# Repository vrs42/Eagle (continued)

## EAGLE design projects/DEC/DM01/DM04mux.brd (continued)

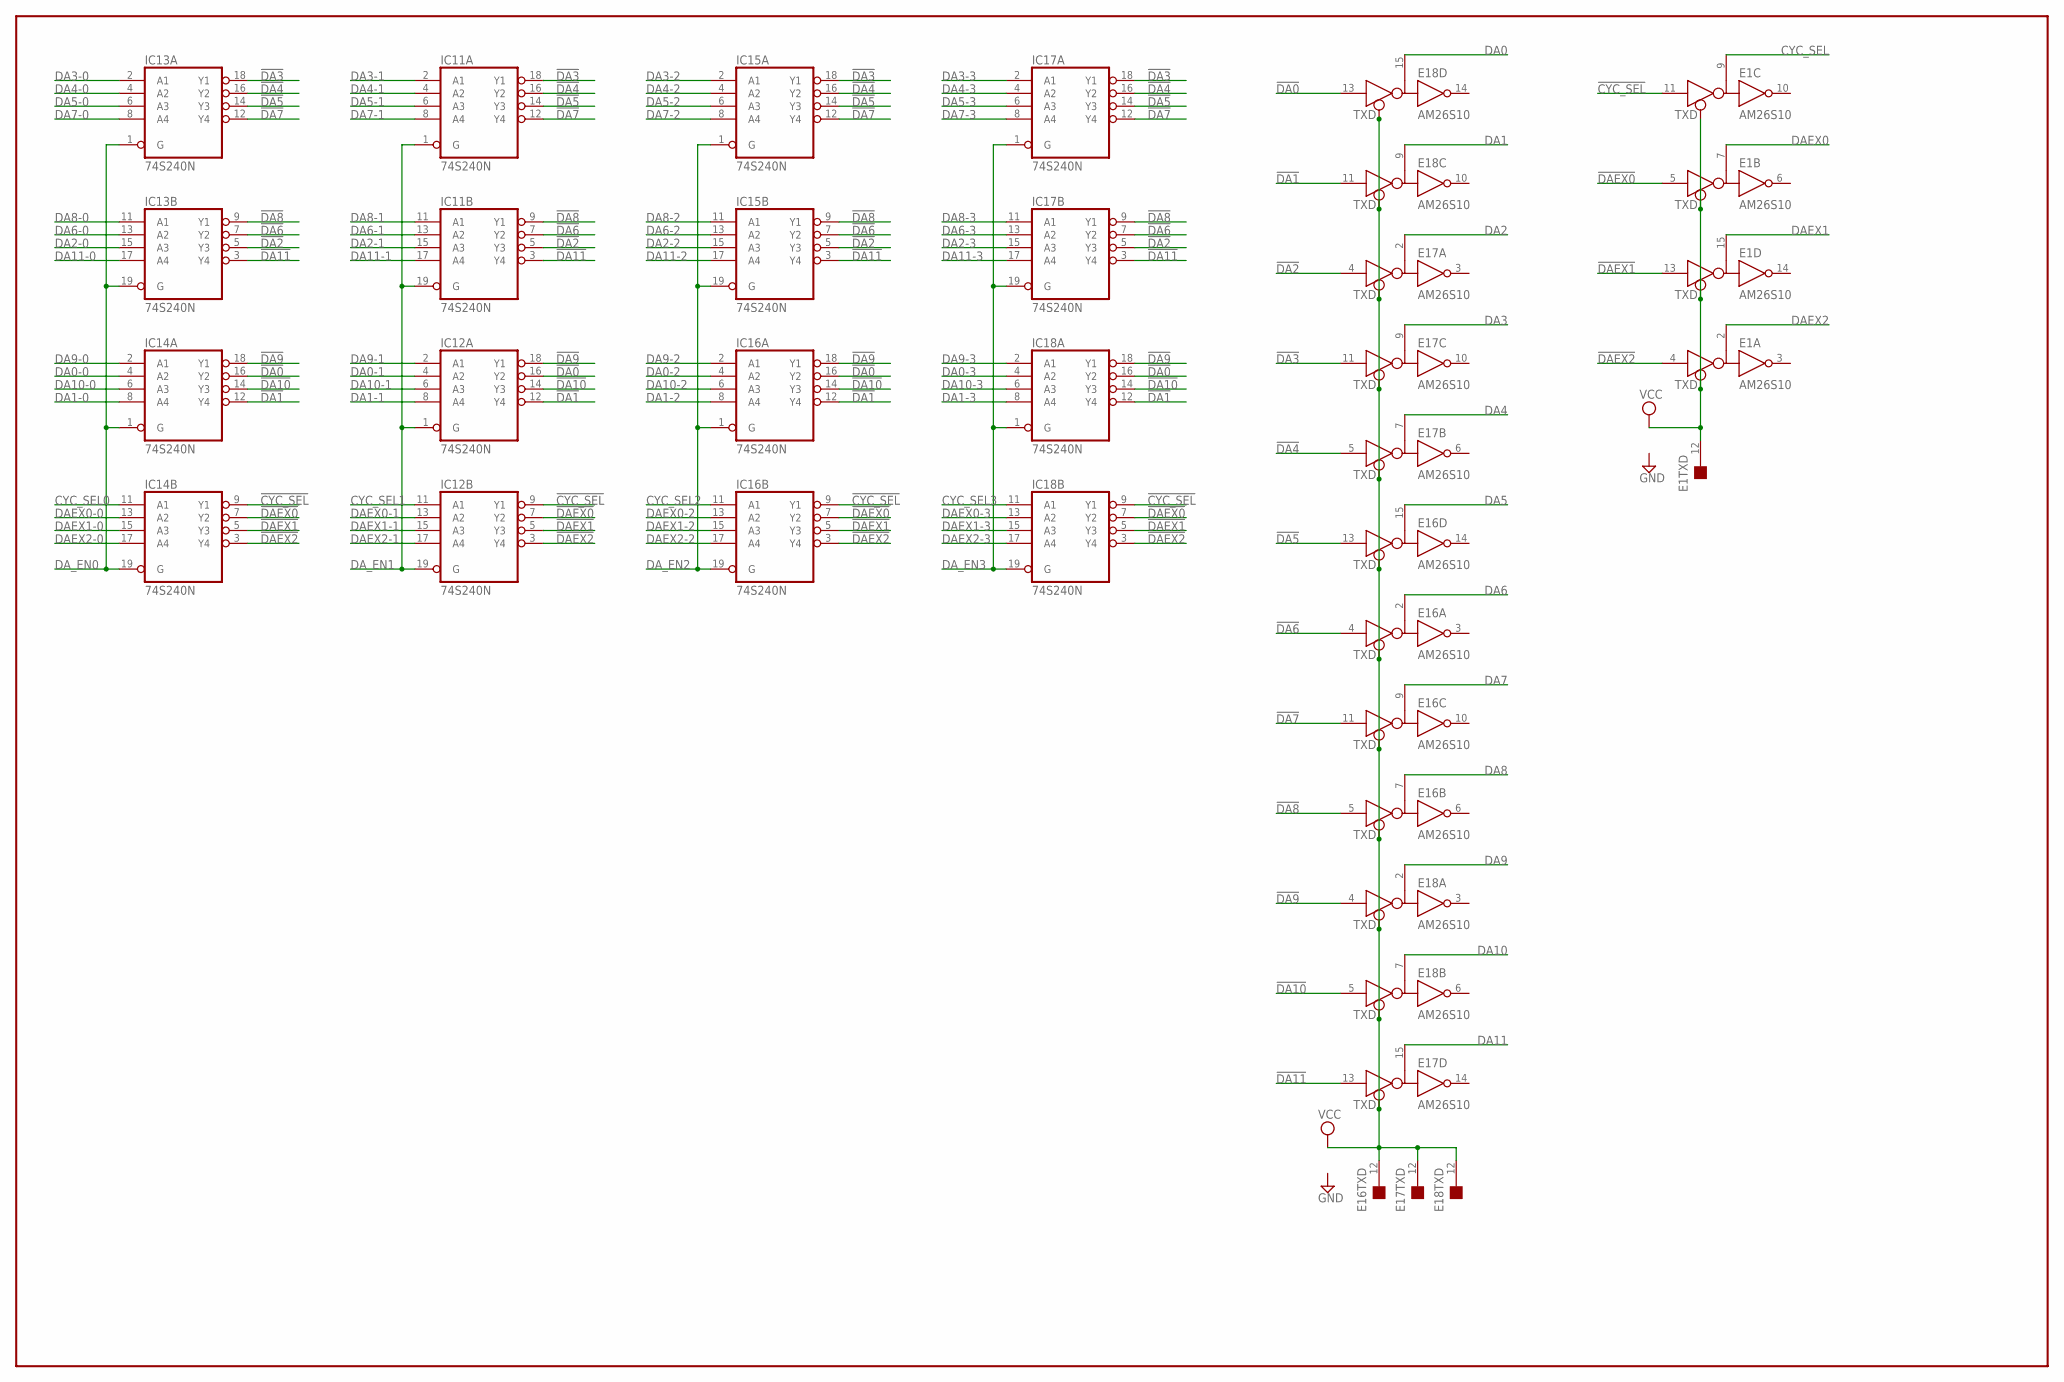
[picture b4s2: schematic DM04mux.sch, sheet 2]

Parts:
E1, E16, E17, E18: AM26S10; DIL16
IC11, IC12, IC13, IC14, IC15, IC16, IC17, IC18: 74S240N; DIL20

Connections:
!CYC_SEL: E1.11 (D), IC12.9 (Y1), IC14.9 (Y1), IC16.9 (Y1), IC18.9 (Y1)
!DA0: E18.13 (D), IC12.16 (Y2), IC14.16 (Y2), IC16.16 (Y2), IC18.16 (Y2)
!DA1: E18.11 (D), IC12.12 (Y4), IC14.12 (Y4), IC16.12 (Y4), IC18.12 (Y4)
!DA2: E17.4 (D), IC11.5 (Y3), IC13.5 (Y3), IC15.5 (Y3), IC17.5 (Y3)
!DA3: E17.11 (D), IC11.18 (Y1), IC13.18 (Y1), IC15.18 (Y1), IC17.18 (Y1)
!DA4: E17.5 (D), IC11.16 (Y2), IC13.16 (Y2), IC15.16 (Y2), IC17.16 (Y2)
!DA5: E16.13 (D), IC11.14 (Y3), IC13.14 (Y3), IC15.14 (Y3), IC17.14 (Y3)
!DA6: E16.4 (D), IC11.7 (Y2), IC13.7 (Y2), IC15.7 (Y2), IC17.7 (Y2)
!DA7: E16.11 (D), IC11.12 (Y4), IC13.12 (Y4), IC15.12 (Y4), IC17.12 (Y4)
!DA8: E16.5 (D), IC11.9 (Y1), IC13.9 (Y1), IC15.9 (Y1), IC17.9 (Y1)
!DA9: E18.4 (D), IC12.18 (Y1), IC14.18 (Y1), IC16.18 (Y1), IC18.18 (Y1)
!DA10: E18.5 (D), IC12.14 (Y3), IC14.14 (Y3), IC16.14 (Y3), IC18.14 (Y3)
!DA11: E17.13 (D), IC11.3 (Y4), IC13.3 (Y4), IC15.3 (Y4), IC17.3 (Y4)
!DAEX0: E1.5 (D), IC12.7 (Y2), IC14.7 (Y2), IC16.7 (Y2), IC18.7 (Y2)
!DAEX1: E1.13 (D), IC12.5 (Y3), IC14.5 (Y3), IC16.5 (Y3), IC18.5 (Y3)
!DAEX2: E1.4 (D), IC12.3 (Y4), IC14.3 (Y4), IC16.3 (Y4), IC18.3 (Y4)
CYC_SEL: E1.9 (B); also elsewhere on the board
CYC_SEL0: IC14.11 (A1); also elsewhere on the board
CYC_SEL1: IC12.11 (A1); also elsewhere on the board
CYC_SEL2: IC16.11 (A1); also elsewhere on the board
CYC_SEL3: IC18.11 (A1); also elsewhere on the board
DA0: E18.15 (B); also elsewhere on the board
DA0-0: IC14.4 (A2); also elsewhere on the board
DA0-1: IC12.4 (A2); also elsewhere on the board
DA0-2: IC16.4 (A2); also elsewhere on the board
DA0-3: IC18.4 (A2); also elsewhere on the board
DA1: E18.9 (B); also elsewhere on the board
DA1-0: IC14.8 (A4); also elsewhere on the board
DA1-1: IC12.8 (A4); also elsewhere on the board
DA1-2: IC16.8 (A4); also elsewhere on the board
DA1-3: IC18.8 (A4); also elsewhere on the board
DA2: E17.2 (B); also elsewhere on the board
DA2-0: IC13.15 (A3); also elsewhere on the board
DA2-1: IC11.15 (A3); also elsewhere on the board
DA2-2: IC15.15 (A3); also elsewhere on the board
DA2-3: IC17.15 (A3); also elsewhere on the board
DA3: E17.9 (B); also elsewhere on the board
DA3-0: IC13.2 (A1); also elsewhere on the board
DA3-1: IC11.2 (A1); also elsewhere on the board
DA3-2: IC15.2 (A1); also elsewhere on the board
DA3-3: IC17.2 (A1); also elsewhere on the board
DA4: E17.7 (B); also elsewhere on the board
DA4-0: IC13.4 (A2); also elsewhere on the board
DA4-1: IC11.4 (A2); also elsewhere on the board
DA4-2: IC15.4 (A2); also elsewhere on the board
DA4-3: IC17.4 (A2); also elsewhere on the board
DA5: E16.15 (B); also elsewhere on the board
DA5-0: IC13.6 (A3); also elsewhere on the board
DA5-1: IC11.6 (A3); also elsewhere on the board
DA5-2: IC15.6 (A3); also elsewhere on the board
DA5-3: IC17.6 (A3); also elsewhere on the board
DA6: E16.2 (B); also elsewhere on the board
DA6-0: IC13.13 (A2); also elsewhere on the board
DA6-1: IC11.13 (A2); also elsewhere on the board
DA6-2: IC15.13 (A2); also elsewhere on the board
DA6-3: IC17.13 (A2); also elsewhere on the board
DA7: E16.9 (B); also elsewhere on the board
DA7-0: IC13.8 (A4); also elsewhere on the board
DA7-1: IC11.8 (A4); also elsewhere on the board
DA7-2: IC15.8 (A4); also elsewhere on the board
DA7-3: IC17.8 (A4); also elsewhere on the board
DA8: E16.7 (B); also elsewhere on the board
DA8-0: IC13.11 (A1); also elsewhere on the board
DA8-1: IC11.11 (A1); also elsewhere on the board
DA8-2: IC15.11 (A1); also elsewhere on the board
DA8-3: IC17.11 (A1); also elsewhere on the board
DA9: E18.2 (B); also elsewhere on the board
DA9-0: IC14.2 (A1); also elsewhere on the board
DA9-1: IC12.2 (A1); also elsewhere on the board
DA9-2: IC16.2 (A1); also elsewhere on the board
DA9-3: IC18.2 (A1); also elsewhere on the board
DA10: E18.7 (B); also elsewhere on the board
DA10-0: IC14.6 (A3); also elsewhere on the board
DA10-1: IC12.6 (A3); also elsewhere on the board
DA10-2: IC16.6 (A3); also elsewhere on the board
DA10-3: IC18.6 (A3); also elsewhere on the board
DA11: E17.15 (B); also elsewhere on the board
DA11-0: IC13.17 (A4); also elsewhere on the board
DA11-1: IC11.17 (A4); also elsewhere on the board
DA11-2: IC15.17 (A4); also elsewhere on the board
DA11-3: IC17.17 (A4); also elsewhere on the board
DAEX0: E1.7 (B); also elsewhere on the board
DAEX0-0: IC14.13 (A2); also elsewhere on the board
DAEX0-1: IC12.13 (A2); also elsewhere on the board
DAEX0-2: IC16.13 (A2); also elsewhere on the board
DAEX0-3: IC18.13 (A2); also elsewhere on the board
DAEX1: E1.15 (B); also elsewhere on the board
DAEX1-0: IC14.15 (A3); also elsewhere on the board
DAEX1-1: IC12.15 (A3); also elsewhere on the board
DAEX1-2: IC16.15 (A3); also elsewhere on the board
DAEX1-3: IC18.15 (A3); also elsewhere on the board
DAEX2: E1.2 (B); also elsewhere on the board
DAEX2-0: IC14.17 (A4); also elsewhere on the board
DAEX2-1: IC12.17 (A4); also elsewhere on the board
DAEX2-2: IC16.17 (A4); also elsewhere on the board
DAEX2-3: IC18.17 (A4); also elsewhere on the board
DA_EN0: IC13.1 (G), IC13.19 (G), IC14.1 (G), IC14.19 (G); also elsewhere on the board
DA_EN1: IC11.1 (G), IC11.19 (G), IC12.1 (G), IC12.19 (G); also elsewhere on the board
DA_EN2: IC15.1 (G), IC15.19 (G), IC16.1 (G), IC16.19 (G); also elsewhere on the board
DA_EN3: IC17.1 (G), IC17.19 (G), IC18.1 (G), IC18.19 (G); also elsewhere on the board
GND: E1.1 (GND), E1.8 (GND), E16.1 (GND), E16.8 (GND), E17.1 (GND), E17.8 (GND), E18.1 (GND), E18.8 (GND), IC11.10 (GND), IC12.10 (GND), IC13.10 (GND), IC14.10 (GND), IC15.10 (GND), IC16.10 (GND), IC17.10 (GND), IC18.10 (GND); also elsewhere on the board
VCC: E1.12 (TXD), E1.16 (VCC), E16.12 (TXD), E16.16 (VCC), E17.12 (TXD), E17.16 (VCC), E18.12 (TXD), E18.16 (VCC), IC11.20 (VCC), IC12.20 (VCC), IC13.20 (VCC), IC14.20 (VCC), IC15.20 (VCC), IC16.20 (VCC), IC17.20 (VCC), IC18.20 (VCC); also elsewhere on the board

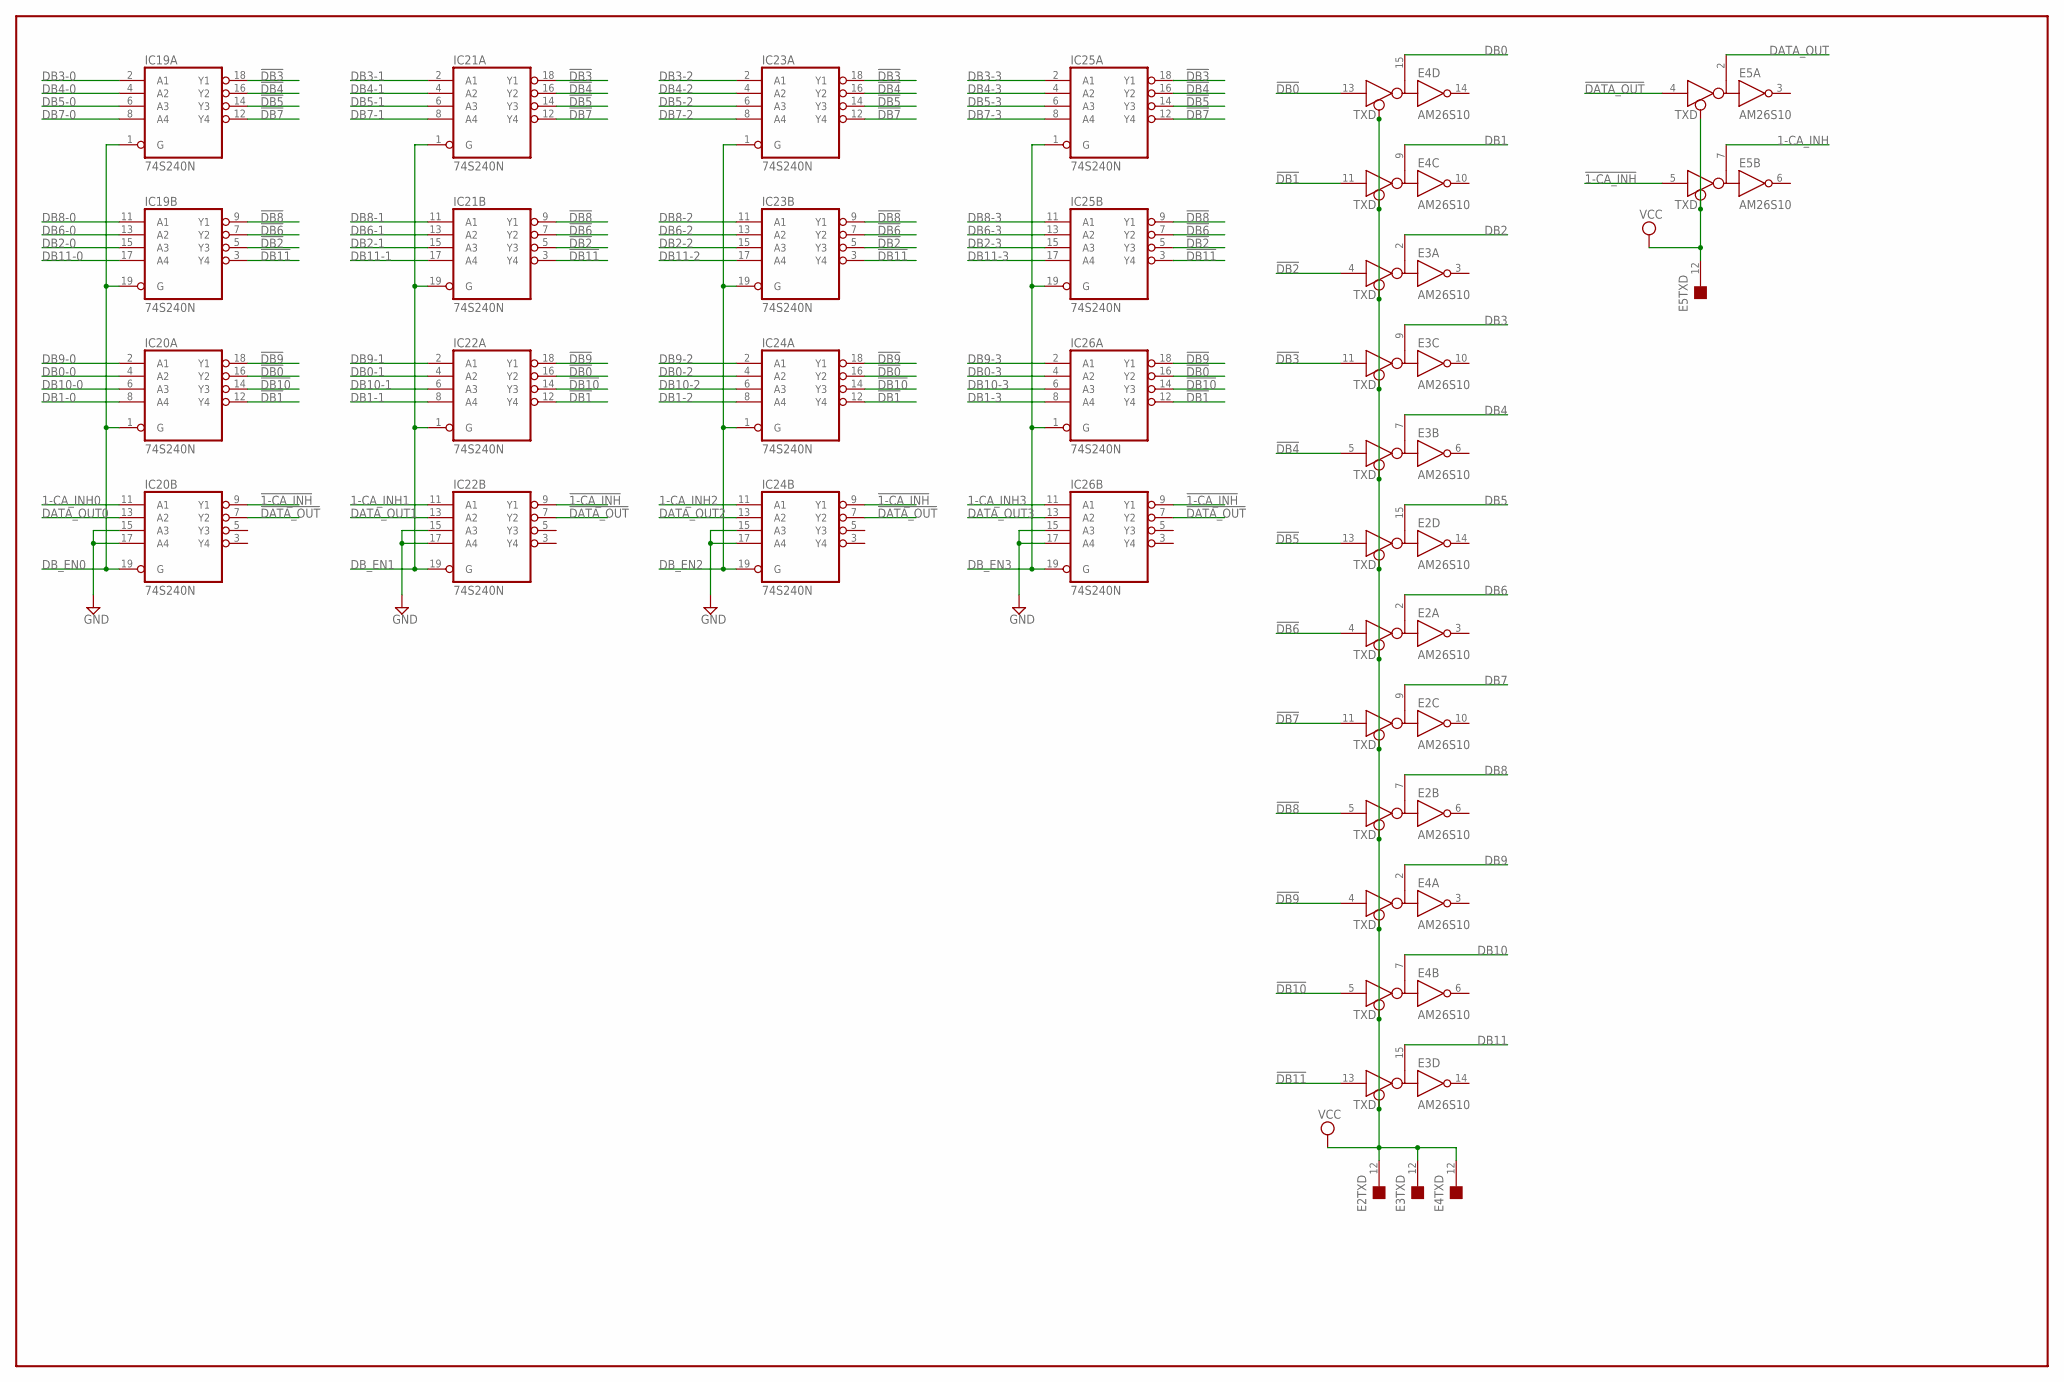
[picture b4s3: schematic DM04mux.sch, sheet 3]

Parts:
E2, E3, E4, E5: AM26S10; DIL16
IC19, IC20, IC21, IC22, IC23, IC24, IC25, IC26: 74S240N; DIL20

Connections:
1-CA_INH: E5.7 (B); also elsewhere on the board
1-CA_INH0: IC20.11 (A1); also elsewhere on the board
1-CA_INH1: IC22.11 (A1); also elsewhere on the board
1-CA_INH2: IC24.11 (A1); also elsewhere on the board
1-CA_INH3: IC26.11 (A1); also elsewhere on the board
!1-CA_INH: E5.5 (D), IC20.9 (Y1), IC22.9 (Y1), IC24.9 (Y1), IC26.9 (Y1)
!DATA_OUT: E5.4 (D), IC20.7 (Y2), IC22.7 (Y2), IC24.7 (Y2), IC26.7 (Y2)
!DB0: E4.13 (D), IC20.16 (Y2), IC22.16 (Y2), IC24.16 (Y2), IC26.16 (Y2)
!DB1: E4.11 (D), IC20.12 (Y4), IC22.12 (Y4), IC24.12 (Y4), IC26.12 (Y4)
!DB2: E3.4 (D), IC19.5 (Y3), IC21.5 (Y3), IC23.5 (Y3), IC25.5 (Y3)
!DB3: E3.11 (D), IC19.18 (Y1), IC21.18 (Y1), IC23.18 (Y1), IC25.18 (Y1)
!DB4: E3.5 (D), IC19.16 (Y2), IC21.16 (Y2), IC23.16 (Y2), IC25.16 (Y2)
!DB5: E2.13 (D), IC19.14 (Y3), IC21.14 (Y3), IC23.14 (Y3), IC25.14 (Y3)
!DB6: E2.4 (D), IC19.7 (Y2), IC21.7 (Y2), IC23.7 (Y2), IC25.7 (Y2)
!DB7: E2.11 (D), IC19.12 (Y4), IC21.12 (Y4), IC23.12 (Y4), IC25.12 (Y4)
!DB8: E2.5 (D), IC19.9 (Y1), IC21.9 (Y1), IC23.9 (Y1), IC25.9 (Y1)
!DB9: E4.4 (D), IC20.18 (Y1), IC22.18 (Y1), IC24.18 (Y1), IC26.18 (Y1)
!DB10: E4.5 (D), IC20.14 (Y3), IC22.14 (Y3), IC24.14 (Y3), IC26.14 (Y3)
!DB11: E3.13 (D), IC19.3 (Y4), IC21.3 (Y4), IC23.3 (Y4), IC25.3 (Y4)
DATA_OUT: E5.2 (B); also elsewhere on the board
DATA_OUT0: IC20.13 (A2); also elsewhere on the board
DATA_OUT1: IC22.13 (A2); also elsewhere on the board
DATA_OUT2: IC24.13 (A2); also elsewhere on the board
DATA_OUT3: IC26.13 (A2); also elsewhere on the board
DB0: E4.15 (B); also elsewhere on the board
DB0-0: IC20.4 (A2); also elsewhere on the board
DB0-1: IC22.4 (A2); also elsewhere on the board
DB0-2: IC24.4 (A2); also elsewhere on the board
DB0-3: IC26.4 (A2); also elsewhere on the board
DB1: E4.9 (B); also elsewhere on the board
DB1-0: IC20.8 (A4); also elsewhere on the board
DB1-1: IC22.8 (A4); also elsewhere on the board
DB1-2: IC24.8 (A4); also elsewhere on the board
DB1-3: IC26.8 (A4); also elsewhere on the board
DB2: E3.2 (B); also elsewhere on the board
DB2-0: IC19.15 (A3); also elsewhere on the board
DB2-1: IC21.15 (A3); also elsewhere on the board
DB2-2: IC23.15 (A3); also elsewhere on the board
DB2-3: IC25.15 (A3); also elsewhere on the board
DB3: E3.9 (B); also elsewhere on the board
DB3-0: IC19.2 (A1); also elsewhere on the board
DB3-1: IC21.2 (A1); also elsewhere on the board
DB3-2: IC23.2 (A1); also elsewhere on the board
DB3-3: IC25.2 (A1); also elsewhere on the board
DB4: E3.7 (B); also elsewhere on the board
DB4-0: IC19.4 (A2); also elsewhere on the board
DB4-1: IC21.4 (A2); also elsewhere on the board
DB4-2: IC23.4 (A2); also elsewhere on the board
DB4-3: IC25.4 (A2); also elsewhere on the board
DB5: E2.15 (B); also elsewhere on the board
DB5-0: IC19.6 (A3); also elsewhere on the board
DB5-1: IC21.6 (A3); also elsewhere on the board
DB5-2: IC23.6 (A3); also elsewhere on the board
DB5-3: IC25.6 (A3); also elsewhere on the board
DB6: E2.2 (B); also elsewhere on the board
DB6-0: IC19.13 (A2); also elsewhere on the board
DB6-1: IC21.13 (A2); also elsewhere on the board
DB6-2: IC23.13 (A2); also elsewhere on the board
DB6-3: IC25.13 (A2); also elsewhere on the board
DB7: E2.9 (B); also elsewhere on the board
DB7-0: IC19.8 (A4); also elsewhere on the board
DB7-1: IC21.8 (A4); also elsewhere on the board
DB7-2: IC23.8 (A4); also elsewhere on the board
DB7-3: IC25.8 (A4); also elsewhere on the board
DB8: E2.7 (B); also elsewhere on the board
DB8-0: IC19.11 (A1); also elsewhere on the board
DB8-1: IC21.11 (A1); also elsewhere on the board
DB8-2: IC23.11 (A1); also elsewhere on the board
DB8-3: IC25.11 (A1); also elsewhere on the board
DB9: E4.2 (B); also elsewhere on the board
DB9-0: IC20.2 (A1); also elsewhere on the board
DB9-1: IC22.2 (A1); also elsewhere on the board
DB9-2: IC24.2 (A1); also elsewhere on the board
DB9-3: IC26.2 (A1); also elsewhere on the board
DB10: E4.7 (B); also elsewhere on the board
DB10-0: IC20.6 (A3); also elsewhere on the board
DB10-1: IC22.6 (A3); also elsewhere on the board
DB10-2: IC24.6 (A3); also elsewhere on the board
DB10-3: IC26.6 (A3); also elsewhere on the board
DB11: E3.15 (B); also elsewhere on the board
DB11-0: IC19.17 (A4); also elsewhere on the board
DB11-1: IC21.17 (A4); also elsewhere on the board
DB11-2: IC23.17 (A4); also elsewhere on the board
DB11-3: IC25.17 (A4); also elsewhere on the board
DB_EN0: IC19.1 (G), IC19.19 (G), IC20.1 (G), IC20.19 (G); also elsewhere on the board
DB_EN1: IC21.1 (G), IC21.19 (G), IC22.1 (G), IC22.19 (G); also elsewhere on the board
DB_EN2: IC23.1 (G), IC23.19 (G), IC24.1 (G), IC24.19 (G); also elsewhere on the board
DB_EN3: IC25.1 (G), IC25.19 (G), IC26.1 (G), IC26.19 (G); also elsewhere on the board
GND: E2.1 (GND), E2.8 (GND), E3.1 (GND), E3.8 (GND), E4.1 (GND), E4.8 (GND), E5.1 (GND), E5.8 (GND), IC19.10 (GND), IC20.10 (GND), IC20.15 (A3), IC20.17 (A4), IC21.10 (GND), IC22.10 (GND), IC22.15 (A3), IC22.17 (A4), IC23.10 (GND), IC24.10 (GND), IC24.15 (A3), IC24.17 (A4), IC25.10 (GND), IC26.10 (GND), IC26.15 (A3), IC26.17 (A4); also elsewhere on the board
VCC: E2.12 (TXD), E2.16 (VCC), E3.12 (TXD), E3.16 (VCC), E4.12 (TXD), E4.16 (VCC), E5.12 (TXD), E5.16 (VCC), IC19.20 (VCC), IC20.20 (VCC), IC21.20 (VCC), IC22.20 (VCC), IC23.20 (VCC), IC24.20 (VCC), IC25.20 (VCC), IC26.20 (VCC); also elsewhere on the board

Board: 2 copper layers, 35 parts (0 on the bottom side), 200 nets, no tracks yet.

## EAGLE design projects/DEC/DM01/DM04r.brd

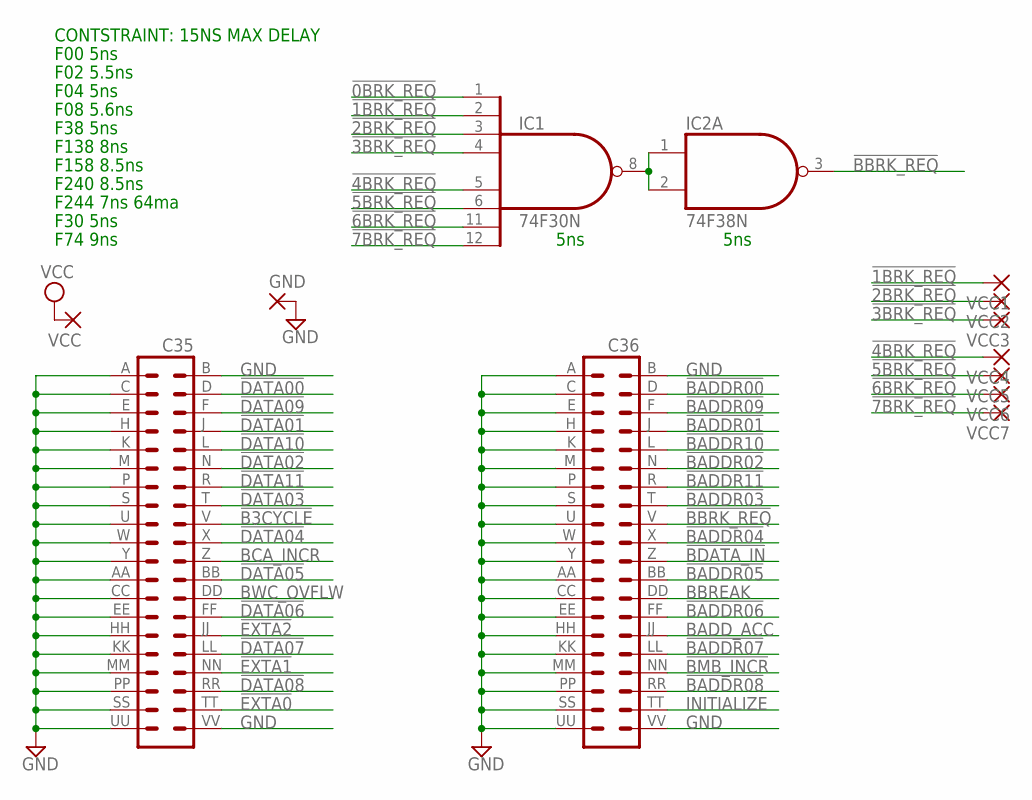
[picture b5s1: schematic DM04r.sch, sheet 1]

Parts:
C35, C36: DEC40PINV
GND: 2,54/0,8
IC1: 74F30N; DIL14
IC2: 74F38N; DIL14
VCC, VCC1, VCC2, VCC3, VCC4, VCC5, VCC6, VCC7: 2,54/0,8

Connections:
!0BRK_REQ: IC1.1 (I0); also elsewhere on the board
!1BRK_REQ: IC1.2 (I1), VCC1.1; also elsewhere on the board
!2BRK_REQ: IC1.3 (I2), VCC2.1; also elsewhere on the board
!3BRK_REQ: IC1.4 (I3), VCC3.1; also elsewhere on the board
!4BRK_REQ: IC1.5 (I4), VCC4.1; also elsewhere on the board
!5BRK_REQ: IC1.6 (I5), VCC5.1; also elsewhere on the board
!6BRK_REQ: IC1.11 (I6), VCC6.1; also elsewhere on the board
!7BRK_REQ: IC1.12 (I7), VCC7.1; also elsewhere on the board
!B3CYCLE: C35.V (18)
!BADDR00: C36.D (4); also elsewhere on the board
!BADDR01: C36.J (8); also elsewhere on the board
!BADDR02: C36.N (12); also elsewhere on the board
!BADDR03: C36.T (16); also elsewhere on the board
!BADDR04: C36.X (20); also elsewhere on the board
!BADDR05: C36.BB (24); also elsewhere on the board
!BADDR06: C36.FF (28); also elsewhere on the board
!BADDR07: C36.LL (32); also elsewhere on the board
!BADDR08: C36.RR (36); also elsewhere on the board
!BADDR09: C36.F (6); also elsewhere on the board
!BADDR10: C36.L (10); also elsewhere on the board
!BADDR11: C36.R (14); also elsewhere on the board
!BBRK_REQ: C36.V (18), IC2.3 (O)
!BDATA_IN: C36.Z (22)
!BMB_INCR: C36.NN (34)
!DATA00: C35.D (4); also elsewhere on the board
!DATA01: C35.J (8); also elsewhere on the board
!DATA02: C35.N (12); also elsewhere on the board
!DATA03: C35.T (16); also elsewhere on the board
!DATA04: C35.X (20); also elsewhere on the board
!DATA05: C35.BB (24); also elsewhere on the board
!DATA06: C35.FF (28); also elsewhere on the board
!DATA07: C35.LL (32); also elsewhere on the board
!DATA08: C35.RR (36); also elsewhere on the board
!DATA09: C35.F (6); also elsewhere on the board
!DATA10: C35.L (10); also elsewhere on the board
!DATA11: C35.R (14); also elsewhere on the board
!EXTA0: C35.TT (38); also elsewhere on the board
!EXTA1: C35.NN (34); also elsewhere on the board
!EXTA2: C35.JJ (30); also elsewhere on the board
BADD_ACC: C36.JJ (30)
BBREAK: C36.DD (26)
BCA_INCR: C35.Z (22)
BWC_OVFLW: C35.DD (26)
GND: C35.A (1), C35.AA (23), C35.B (2), C35.C (3), C35.CC (25), C35.E (5), C35.EE (27), C35.H (7), C35.HH (29), C35.K (9), C35.KK (31), C35.M (11), C35.MM (33), C35.P (13), C35.PP (35), C35.S (15), C35.SS (37), C35.U (17), C35.UU (39), C35.VV (40), C35.W (19), C35.Y (21), C36.A (1), C36.AA (23), C36.B (2), C36.C (3), C36.CC (25), C36.E (5), C36.EE (27), C36.H (7), C36.HH (29), C36.K (9), C36.KK (31), C36.M (11), C36.MM (33), C36.P (13), C36.PP (35), C36.S (15), C36.SS (37), C36.U (17), C36.UU (39), C36.VV (40), C36.W (19), C36.Y (21), GND.1, IC1.7 (GND), IC2.7 (GND); also elsewhere on the board
INITIALIZE: C36.TT (38); also elsewhere on the board
unnamed: IC1.8 (O), IC2.1 (I0), IC2.2 (I1)
VCC: IC1.14 (VCC), IC2.14 (VCC), VCC.1; also elsewhere on the board

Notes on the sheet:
CONTSTRAINT: 15NS MAX DELAY
F04 5ns
F38 5ns
F00 5ns
F02 5.5ns
F138 8ns
F158 8.5ns
F240 8.5ns
F244 7ns 64ma
F08 5.6ns
F74 9ns
F30 5ns
5ns

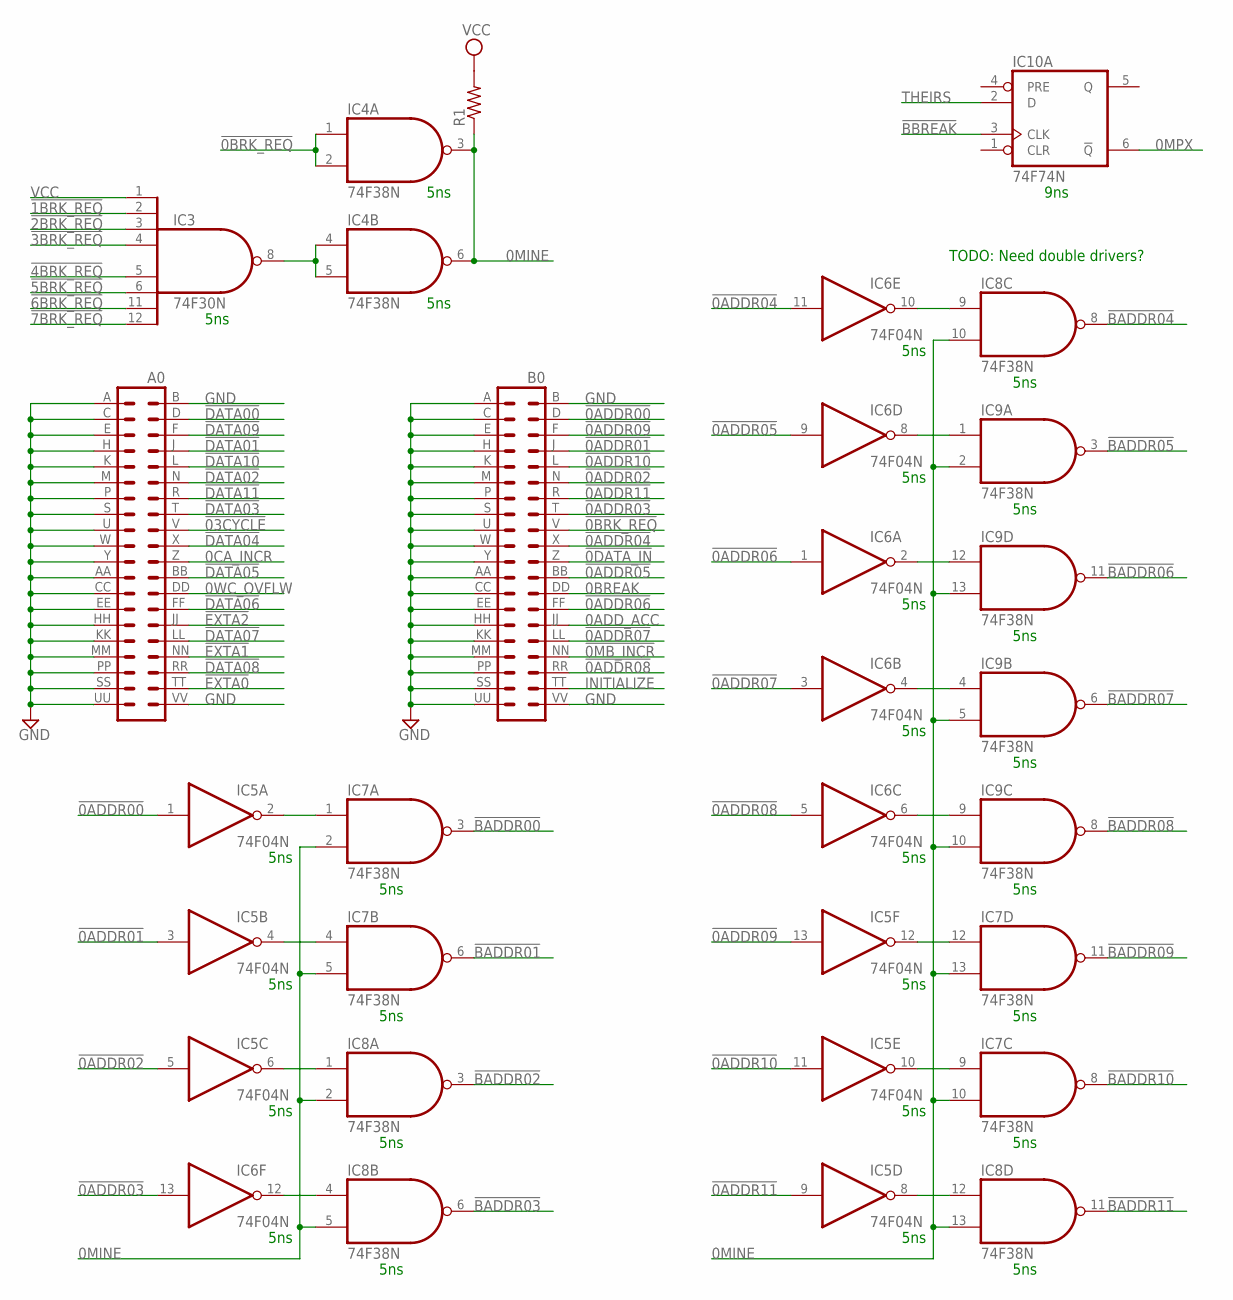
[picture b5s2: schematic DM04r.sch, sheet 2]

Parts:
A0: DEC40PINV
B0: DEC40PINV
IC3: 74F30N; DIL14
IC4, IC7, IC8, IC9: 74F38N; DIL14
IC5, IC6: 74F04N; DIL14
IC10: 74F74N; DIL14
R1: R-US_0207/10; 0207/10

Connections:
0ADD_ACC: B0.JJ (30)
0BREAK: B0.DD (26)
0CA_INCR: A0.Z (22)
0MINE: IC4.3 (O), IC4.6 (O), IC7.2 (I1), IC7.5 (I1), IC7.10 (I1), IC7.13 (I1), IC8.2 (I1), IC8.5 (I1), IC8.10 (I1), IC8.13 (I1), IC9.2 (I1), IC9.5 (I1), IC9.10 (I1), IC9.13 (I1), R1.1
0MPX: IC10.6 (!Q)
0WC_OVFLW: A0.DD (26)
!0ADDR00: B0.D (4), IC5.1 (I)
!0ADDR01: B0.J (8), IC5.3 (I)
!0ADDR02: B0.N (12), IC5.5 (I)
!0ADDR03: B0.T (16), IC6.13 (I)
!0ADDR04: B0.X (20), IC6.11 (I)
!0ADDR05: B0.BB (24), IC6.9 (I)
!0ADDR06: B0.FF (28), IC6.1 (I)
!0ADDR07: B0.LL (32), IC6.3 (I)
!0ADDR08: B0.RR (36), IC6.5 (I)
!0ADDR09: B0.F (6), IC5.13 (I)
!0ADDR10: B0.L (10), IC5.11 (I)
!0ADDR11: B0.R (14), IC5.9 (I)
!0BRK_REQ: B0.V (18), IC4.1 (I0), IC4.2 (I1); also elsewhere on the board
!0DATA_IN: B0.Z (22)
!0MB_INCR: B0.NN (34)
!1BRK_REQ: IC3.2 (I1); also elsewhere on the board
!2BRK_REQ: IC3.3 (I2); also elsewhere on the board
!3BRK_REQ: IC3.4 (I3); also elsewhere on the board
!03CYCLE: A0.V (18)
!4BRK_REQ: IC3.5 (I4); also elsewhere on the board
!5BRK_REQ: IC3.6 (I5); also elsewhere on the board
!6BRK_REQ: IC3.11 (I6); also elsewhere on the board
!7BRK_REQ: IC3.12 (I7); also elsewhere on the board
!BADDR00: IC7.3 (O); also elsewhere on the board
!BADDR01: IC7.6 (O); also elsewhere on the board
!BADDR02: IC8.3 (O); also elsewhere on the board
!BADDR03: IC8.6 (O); also elsewhere on the board
!BADDR04: IC8.8 (O); also elsewhere on the board
!BADDR05: IC9.3 (O); also elsewhere on the board
!BADDR06: IC9.11 (O); also elsewhere on the board
!BADDR07: IC9.6 (O); also elsewhere on the board
!BADDR08: IC9.8 (O); also elsewhere on the board
!BADDR09: IC7.11 (O); also elsewhere on the board
!BADDR10: IC7.8 (O); also elsewhere on the board
!BADDR11: IC8.11 (O); also elsewhere on the board
!BBREAK: IC10.3 (CLK)
!DATA00: A0.D (4); also elsewhere on the board
!DATA01: A0.J (8); also elsewhere on the board
!DATA02: A0.N (12); also elsewhere on the board
!DATA03: A0.T (16); also elsewhere on the board
!DATA04: A0.X (20); also elsewhere on the board
!DATA05: A0.BB (24); also elsewhere on the board
!DATA06: A0.FF (28); also elsewhere on the board
!DATA07: A0.LL (32); also elsewhere on the board
!DATA08: A0.RR (36); also elsewhere on the board
!DATA09: A0.F (6); also elsewhere on the board
!DATA10: A0.L (10); also elsewhere on the board
!DATA11: A0.R (14); also elsewhere on the board
!EXTA0: A0.TT (38); also elsewhere on the board
!EXTA1: A0.NN (34); also elsewhere on the board
!EXTA2: A0.JJ (30); also elsewhere on the board
GND: A0.A (1), A0.AA (23), A0.B (2), A0.C (3), A0.CC (25), A0.E (5), A0.EE (27), A0.H (7), A0.HH (29), A0.K (9), A0.KK (31), A0.M (11), A0.MM (33), A0.P (13), A0.PP (35), A0.S (15), A0.SS (37), A0.U (17), A0.UU (39), A0.VV (40), A0.W (19), A0.Y (21), B0.A (1), B0.AA (23), B0.B (2), B0.C (3), B0.CC (25), B0.E (5), B0.EE (27), B0.H (7), B0.HH (29), B0.K (9), B0.KK (31), B0.M (11), B0.MM (33), B0.P (13), B0.PP (35), B0.S (15), B0.SS (37), B0.U (17), B0.UU (39), B0.VV (40), B0.W (19), B0.Y (21), IC3.7 (GND), IC4.7 (GND), IC5.7 (GND), IC6.7 (GND), IC7.7 (GND), IC8.7 (GND), IC9.7 (GND), IC10.7 (GND); also elsewhere on the board
INITIALIZE: B0.TT (38); also elsewhere on the board
unnamed: IC6.10 (O), IC8.9 (I0)
unnamed: IC3.8 (O), IC4.4 (I0), IC4.5 (I1)
unnamed: IC6.8 (O), IC9.1 (I0)
unnamed: IC6.2 (O), IC9.12 (I0)
unnamed: IC6.4 (O), IC9.4 (I0)
unnamed: IC6.6 (O), IC9.9 (I0)
unnamed: IC5.12 (O), IC7.12 (I0)
unnamed: IC5.10 (O), IC7.9 (I0)
unnamed: IC5.8 (O), IC8.12 (I0)
unnamed: IC5.2 (O), IC7.1 (I0)
unnamed: IC5.4 (O), IC7.4 (I0)
unnamed: IC5.6 (O), IC8.1 (I0)
unnamed: IC6.12 (O), IC8.4 (I0)
THEIRS: IC10.2 (D)
VCC: IC3.1 (I0), IC3.14 (VCC), IC4.14 (VCC), IC5.14 (VCC), IC6.14 (VCC), IC7.14 (VCC), IC8.14 (VCC), IC9.14 (VCC), IC10.14 (VCC), R1.2; also elsewhere on the board

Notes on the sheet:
5ns
TODO: Need double drivers?
9ns

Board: 2 copper layers, 24 parts (0 on the bottom side), 66 nets, no tracks yet.
